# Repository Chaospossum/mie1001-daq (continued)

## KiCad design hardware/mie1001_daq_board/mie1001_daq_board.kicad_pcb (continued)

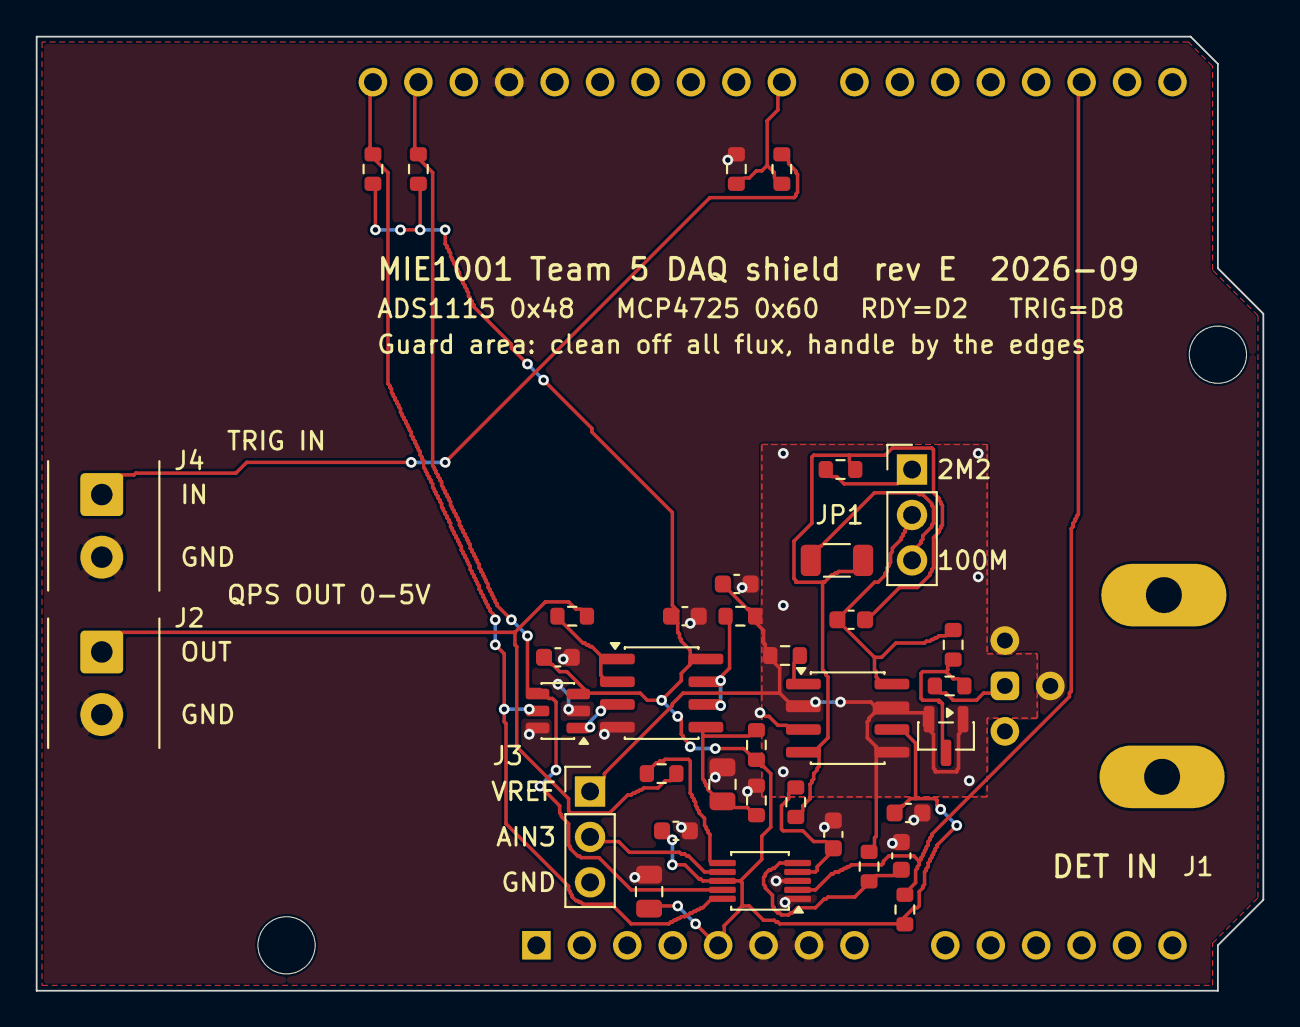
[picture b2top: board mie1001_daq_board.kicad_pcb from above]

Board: 2 copper layers, 68.6 x 53.3 mm, 40 parts (1 on the bottom side), 24 nets.

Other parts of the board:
H1, H2: MountingHole_3.2mm_M3

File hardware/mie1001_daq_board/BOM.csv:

Qty,References,Value,Footprint,Manufacturer,MPN,Digi-Key P/N,LCSC,Note
1,A1,Arduino UNO R3,Module:Arduino_UNO_R3,Arduino,A000066,1050-1024-ND,,
1,C1,10pF C0G 50V 0603,Capacitor_SMD:C_0603_1608Metric,Murata,GRM1885C1H100JA01D,490-1403-1-ND,C1634,"MUST be fitted. TIA stability needs Cf >= sqrt(Cin/(2*pi*Rf*GBW)); with ~100 pF of cable, Rf = 2M2 and the LMP7721's 17 MHz GBW that is ~0.65 pF, so 10 pF has wide margin (sets a 7.2 kHz / 159 Hz pole)."
3,"C2, C9, C10",1uF X5R 50V 0603,Capacitor_SMD:C_0603_1608Metric,Samsung,CL10A105KB8NNNC,1276-1860-1-ND,C15849,Any 1 uF >=16 V X5R/X7R 0603 works; confirm JLCPCB stock of C15849 when ordering.
2,"C3, C7",10uF X5R 25V 0805,Capacitor_SMD:C_0805_2012Metric,Samsung,CL21A106KAYNNNE,1276-2891-1-ND,C15850,
4,"C4, C5, C6, C8",100nF X7R 50V 0603,Capacitor_SMD:C_0603_1608Metric,Samsung,CL10B104KB8NNNC,1276-1000-1-ND,C14663,
1,D1,BAV199LT1G,Package_TO_SOT_SMD:SOT-23,onsemi,BAV199LT1G,BAV199LT1GOSCT-ND,C145516,"Tied to VREF, not the rails: 0 V bias means near-zero leakage into the pA node (20-50 pA per diode at 2.5 V reverse)."
1,J1,"Detector in, BNC",Connector_Coaxial:BNC_Amphenol_031-6575_Horizontal,Amphenol RF,031-6575,ARF2111-ND,,
1,J2,QPS mass cmd out,"TerminalBlock_Phoenix:TerminalBlock_Phoenix_PT-1,5-2-3.5-H_1x02_P3.50mm_Horizontal",Phoenix Contact,1984617,277-1721-ND,,
1,J3,VREF / AIN3 / GND,Connector_PinHeader_2.54mm:PinHeader_1x03_P2.54mm_Vertical,Sullins,PRPC040SAAN-RC,S1011EC-40-ND,,
1,J4,Trigger in,"TerminalBlock_Phoenix:TerminalBlock_Phoenix_PT-1,5-2-3.5-H_1x02_P3.50mm_Horizontal",Phoenix Contact,1984617,277-1721-ND,,
1,JP1,TIA range select,Connector_PinHeader_2.54mm:PinHeader_1x03_P2.54mm_Vertical,Sullins,PRPC040SAAN-RC,S1011EC-40-ND,,
1,R1,2M2 1% 0603,Resistor_SMD:R_0603_1608Metric,Yageo,RC0603FR-072M2L,YAG3329CT-ND,C22938,
1,R2,100M 1% 1206,Resistor_SMD:R_1206_3216Metric,Stackpole,HVCB1206FKC100M,HVCB1206FKC100MCT-ND,C59781,"High-value TIA feedback: guard the pads, keep them clean, no flux residue. JLC/LCSC has no HVCB stock: use Uniroyal 1206W4F1006T5E (C59781), 1% +-100 ppm/C."
6,"R3, R4, R9, R13, R16, R17",1k 1% 0603,Resistor_SMD:R_0603_1608Metric,Yageo,RC0603FR-071KL,311-1.00KHRCT-ND,C21190,Protects the LMP7721 IN+ from transients on VREF; carries only fA.
2,"R5, R6",4k7 1% 0603,Resistor_SMD:R_0603_1608Metric,Yageo,RC0603FR-074K7L,311-4.70KHRCT-ND,C23162,
4,"R7, R8, R10, R11",10k 1% 0603,Resistor_SMD:R_0603_1608Metric,Yageo,RC0603FR-0710KL,311-10.0KHRCT-ND,C25804,ALERT/RDY is open-drain - this pull-up is required
2,"R12, R15",100R 1% 0603,Resistor_SMD:R_0603_1608Metric,Yageo,RC0603FR-07100RL,311-100HRCT-ND,C22775,Isolation resistor: MCP6002 driving >100 pF of cable needs Riso (DS20001733L section 4.3). Isolation resistor so the MCP6002 VREF buffer can drive C9.
1,R14,10k 1% 0603 anti-surge,Resistor_SMD:R_0603_1608Metric,Panasonic,ERJ-PA3F1002V,P10KBYCT-ND,,"Series protection at the BNC: anti-surge (pulse-rated, AEC-Q200) 0603, limits the current into D1. 10 uV drop per nA. HAND-SOLDER from the Digi-Key order (not in the JLC assembly files)."
1,U1,MCP4725A0T-E/CH,Package_TO_SOT_SMD:SOT-23-6,Microchip,MCP4725A0T-E/CH,MCP4725A0T-E/CHCT-ND,C144198,
1,U2,ADS1115IDGSR,Package_SO:MSOP-10_3x3mm_P0.5mm,Texas Instruments,ADS1115IDGSR,296-38849-1-ND,C37593,
1,U3,MCP6002-I/SN,Package_SO:SOIC-8_3.9x4.9mm_P1.27mm,Microchip,MCP6002-I/SN,MCP6002-I/SN-ND,C116706,
1,U4,LMP7721MA/NOPB,Package_SO:SOIC-8_3.9x4.9mm_P1.27mm,Texas Instruments,LMP7721MA/NOPB,LMP7721MA/NOPB-ND,C124427,"Electrometer TIA. Guard ring (VREF) on both layers around pins 1/8 and the feedback parts, no solder mask there. Clean flux off after soldering."

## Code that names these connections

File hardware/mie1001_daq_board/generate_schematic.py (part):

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    pin("8", "VDD", -17.78, 6.35, 0, "power_in"),
    pin("9", "SDA", -17.78, 3.81, 0, "bidirectional"),
    pin("10", "SCL", -17.78, 1.27, 0, "input"),
    pin("2", "ALERT/RDY", -17.78, -1.27, 0, "open_collector"),
    pin("1", "ADDR", -17.78, -3.81, 0, "input"),
    pin("3", "GND", -17.78, -6.35, 0, "power_in"),
    pin("4", "AIN0", 17.78, 3.81, 180, "passive"),
    pin("5", "AIN1", 17.78, 1.27, 180, "passive"),
    pin("6", "AIN2", 17.78, -1.27, 180, "passive"),
    pin("7", "AIN3", 17.78, -3.81, 180, "passive"),
], {1: [rect(-12.7, 8.89, 12.7, -8.89)]},
    dict(Reference="U", Value="ADS1115IDGSR",
         Footprint="Package_SO:MSOP-10_3x3mm_P0.5mm",
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           hide_numbers=True, name_offset=0)

# ---- connectors (pins on the LEFT: signal arrives from the left, body to the right)
defsym("DAQ:BNC", [pin("1", "SIG", -11.43, 1.27, 0), pin("2", "SHIELD", -11.43, -1.27, 0),
                   # pads 3 and 4 are the other two outer-contact legs: stacked on pin 2 so all three reach GND
                   pin("3", "SHIELD", -11.43, -1.27, 0, hide=True), pin("4", "SHIELD", -11.43, -1.27, 0, hide=True)],
       {1: [rect(-6.35, 3.81, 6.35, -3.81)]},
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
R14 = place("R14", "DAQ:R", 46.99, 68.58, 90, fields=F("R14"),
            ref_at=(46.99, 64.77), val_at=(46.99, 73.66))
wire(J1.p(1), R14.p(1)); label("BNC_IN", (40.64, 68.58))   # series R before the clamp
wire(R14.p(2), (53.34, 68.58))
wire((53.34, 68.58), (53.34, 88.9))                 # down to the clamp
junction((53.34, 68.58))
label("DET_IN", (53.34, 78.74))
wire(J1.p(2), (44.45, 71.12), (44.45, 82.55)); pwr("GND", (44.45, 82.55))
# both outer ends of the BAV199 go to VREF: back-to-back clamp at 0 V bias (near-zero leakage)
wire(D1.p(1), (76.2, 90.17), (81.28, 90.17))
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text("guard = VREF", 99.06, 96.52, 1.0)
C8 = place("C8", "DAQ:C", 142.24, 93.98, fields=F("C8"), ref_at=(144.78, 92.71), val_at=(144.78, 95.25), just="left")
pwr("+5V", C8.p(1)); pwr("GND", C8.p(2))
# TIA_IN rail runs up from the inverting input and feeds JP1 pin 2 directly
wire((83.82, 68.58), (83.82, 45.72), (110.49, 45.72))
junction((83.82, 68.58))
label("TIA_IN", (83.82, 52.07))

C1 = place("C1", "DAQ:C", 93.98, 63.5, 90, fields=F("C1"),
           ref_at=(93.98, 59.69), val_at=(93.98, 67.31))
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           ref_at=(127.0, 30.48), val_at=(127.0, 35.56), just="left")
R2 = place("R2", "DAQ:R_1206", 116.84, 58.42, 90, fields=F("R2"),
           ref_at=(127.0, 55.88), val_at=(127.0, 60.96), just="left")
wire(JP1.p(1), (106.68, 43.18), (106.68, 33.02), R1.p(1)); label("RF_2M2", (106.68, 38.1))
wire(R1.p(2), (139.7, 33.02))
wire(JP1.p(3), (104.14, 48.26), (104.14, 58.42), R2.p(1)); label("RF_100M", (104.14, 53.34), justify="right bottom")
wire(R2.p(2), (139.7, 58.42))
wire((139.7, 33.02), (139.7, 71.12))                # TIA_OUT rail
junction((139.7, 58.42), (139.7, 63.5), (139.7, 71.12))
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
R3 = place("R3", "DAQ:R", 157.48, 71.12, 90, fields=F("R3"), ref_at=(157.48, 67.31), val_at=(157.48, 63.5))
C2 = place("C2", "DAQ:C", 167.64, 78.74, fields=F("C2"), ref_at=(171.45, 77.47), val_at=(171.45, 80.01), just="left")
wire(U4.p("4"), R3.p(1)); label("TIA_OUT", (146.05, 71.12))
wire(R3.p(2), (177.8, 71.12))
label("ADC_IN", (177.8, 90.17))
wire(C2.p(1), (167.64, 71.12)); junction((167.64, 71.12))
wire(C2.p(2), (167.64, 83.82)); pwr("GND", (167.64, 83.82))
text("TIA (U4 LMP7721):  Vout = VREF +/- I_det x Rf\n"
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           ref_at=(337.82, 50.8), val_at=(337.82, 59.69))
R10 = place("R10", "DAQ:R", 322.58, 62.23, fields=F("R10"), ref_at=(325.12, 60.96),
            val_at=(325.12, 63.5), just="left")
wire(J4.p(1), R9.p(2)); label("TRIG_EXT", (344.17, 54.61))
wire(R9.p(1), A1.p("23")); label("TRIG", (327.66, 54.61))
wire(J4.p(2), (349.25, 57.15), (349.25, 66.04)); pwr("GND", (349.25, 66.04))
wire(R10.p(1), (322.58, 54.61)); junction((322.58, 54.61))
wire(R10.p(2), (322.58, 72.39)); pwr("GND", (322.58, 72.39))
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wire((88.9, 132.08), (88.9, 123.19), (63.5, 123.19), U3C.p("6"))
R15 = place("R15", "DAQ:R", 96.52, 132.08, 90, fields=F("R15"),
            ref_at=(96.52, 128.27), val_at=(96.52, 136.53))
wire((88.9, 132.08), R15.p(1)); junction((88.9, 132.08)); label("VREF_BUF", (88.9, 127.0))
C9 = place("C9", "DAQ:C", 104.14, 137.16, fields=F("C9"), ref_at=(106.68, 135.89), val_at=(106.68, 138.43), just="left")
wire(C9.p(1), (104.14, 132.08)); junction((104.14, 132.08)); pwr("GND", C9.p(2))
label("VREF_DIV", (33.02, 137.16))
text("VREF = 5V x R8/(R7+R8) = 2.50 V, C3 filters USB ripple.\nU3B buffers it; R15 lets it drive C9.\nFeeds R17 -> TIA IN+, the guard, D1 and AIN1.",
     59.69, 143.51, 1.0)

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wire(U2.p("9"), (121.92, 132.08), (121.92, 101.6), (251.46, 101.6))
wire(U2.p("10"), (119.38, 134.62), (119.38, 99.06), (256.54, 99.06))
wire(U2.p("2"), (113.03, 137.16), (113.03, 110.49), (316.23, 110.49))
label("SDA", (200.66, 101.6)); label("SCL", (200.66, 99.06)); label("RDY", (200.66, 110.49))
wire(U2.p("1"), (130.81, 139.7), (130.81, 142.24), U2.p("3"))
wire((130.81, 142.24), (130.81, 149.86)); junction((130.81, 142.24))
pwr("GND", (130.81, 149.86))
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           ref_at=(207.01, 138.43), val_at=(207.01, 140.97))
R13 = place("R13", "DAQ:R", 180.34, 137.16, 90, fields=F("R13"),
            ref_at=(180.34, 140.97), val_at=(180.34, 143.51))
wire(U2.p("6"), R13.p(1)); label("AIN2", (171.45, 137.16))   # AIN2 reads back the QPS command
wire(R13.p(2), (186.69, 137.16)); label("QPS_OUT", (186.69, 137.16))
wire(U2.p("7"), (187.96, 139.7), (187.96, 148.59), J3.p(2)); label("AIN3", (187.96, 144.78), justify="right bottom")
wire(U2.p("4"), (177.8, 132.08), (177.8, 71.12))
wire(J3.p(3), (186.69, 151.13), (186.69, 158.75)); pwr("GND", (186.69, 158.75))

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R17 = place("R17", "DAQ:R", 96.52, 81.28, 0, fields=F("R17"),
            ref_at=(99.06, 80.01), val_at=(99.06, 82.55), just="left")
wire((109.22, 107.95), (96.52, 107.95), R17.p(2))    # VREF up to R17; clamp and guard tap below it
wire(R17.p(1), (96.52, 73.66), U4.p("1")); label("TIA_REF", (99.06, 73.66))
wire((109.22, 107.95), (193.04, 107.95), (193.04, 146.05), J3.p(1))
junction((109.22, 107.95))
R16 = place("R16", "DAQ:R", 187.96, 134.62, 90, fields=F("R16"),
            ref_at=(187.96, 130.81), val_at=(187.96, 138.43))
C10 = place("C10", "DAQ:C", 180.34, 130.81, 180, fields=F("C10"), ref_at=(182.88, 129.54), val_at=(182.88, 132.08), just="left")
wire(U2.p("5"), R16.p(1)); label("AIN1", (172.72, 134.62))
junction(C10.p(1)); pwr("GND", C10.p(2), 180)
junction((193.04, 134.62))
label("VREF", (140.97, 107.95))
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U3A = place("U3", "DAQ:MCP6002", 312.42, 132.08, unit=1, fields=F("U3"),
            ref_at=(311.15, 123.19), val_at=(311.15, 125.73), show_value=False)
wire(U1.p("1"), (292.1, 132.08), (292.1, 134.62), U3A.p("3"))
label("DAC_OUT", (285.75, 132.08))
wire(U3A.p("1"), (330.2, 132.08))
wire((330.2, 132.08), (330.2, 123.19), (302.26, 123.19), U3A.p("2")); label("BUF_OUT", (309.88, 123.19))
J2 = place("J2", "DAQ:Screw_Terminal_1x02", 361.95, 132.08, fields=F("J2"),
           ref_at=(361.95, 124.46), val_at=(361.95, 127.0))
R12 = place("R12", "DAQ:R", 337.82, 132.08, 90, fields=F("R12"),
            ref_at=(337.82, 128.27), val_at=(337.82, 137.16))
wire((330.2, 132.08), R12.p(1)); junction((330.2, 132.08))
wire(R12.p(2), (347.98, 132.08), (347.98, 130.81), J2.p(1))
label("QPS_OUT", (342.9, 132.08))
wire(J2.p(2), (345.44, 133.35), (345.44, 142.24)); pwr("GND", (345.44, 142.24))
text("U3A buffers the DAC (gain = 1) -> 0-5 V mass command. R12 isolates the cable.\n"
     "A 0-10 V Extrel command needs a separate >=12 V rail\n"
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 "JP1  1-2 = CEM range     Rf = R1 2M2    full scale 1.14 uA,  57 pA/LSB\n"
 "     2-3 = Faraday range Rf = R2 100M   full scale 25 nA,  1.25 pA/LSB\n"
 "I2C  ADS1115 = 0x48 (ADDR->GND)   MCP4725 = 0x60 (A0->GND)\n"
 "UNO  D2 = ALERT/RDY    D8 = trigger    SDA/SCL pins = I2C.  Every other UNO pin is free.",
 172.72, 229.87, 1.05)

# ----------------------------------------------------------------------------- emit
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
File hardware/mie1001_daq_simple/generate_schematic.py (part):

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    pin("8", "VDD", -17.78, 6.35, 0, "power_in"),
    pin("9", "SDA", -17.78, 3.81, 0, "bidirectional"),
    pin("10", "SCL", -17.78, 1.27, 0, "input"),
    pin("2", "ALERT/RDY", -17.78, -1.27, 0, "open_collector"),
    pin("1", "ADDR", -17.78, -3.81, 0, "input"),
    pin("3", "GND", -17.78, -6.35, 0, "power_in"),
    pin("4", "AIN0", 17.78, 3.81, 180, "passive"),
    pin("5", "AIN1", 17.78, 1.27, 180, "passive"),
    pin("6", "AIN2", 17.78, -1.27, 180, "passive"),
    pin("7", "AIN3", 17.78, -3.81, 180, "passive"),
], {1: [rect(-12.7, 8.89, 12.7, -8.89)]},
    dict(Reference="U", Value="ADS1115IDGSR",
         Footprint="Package_SO:MSOP-10_3x3mm_P0.5mm",
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           hide_numbers=True, name_offset=0)

# ---- connectors (pins on the LEFT: signal arrives from the left, body to the right)
defsym("DAQ:BNC", [pin("1", "SIG", -11.43, 1.27, 0), pin("2", "SHIELD", -11.43, -1.27, 0),
                   # pads 3 and 4 are the other two outer-contact legs: stacked on pin 2 so all three reach GND
                   pin("3", "SHIELD", -11.43, -1.27, 0, hide=True), pin("4", "SHIELD", -11.43, -1.27, 0, hide=True)],
       {1: [rect(-6.35, 3.81, 6.35, -3.81)]},
       dict(Reference="J", Value="BNC", Footprint="Connector_Coaxial:BNC_Amphenol_031-6575_Horizontal",
            Datasheet="", Description="BNC coaxial jack, horizontal PCB mount"))
defsym("DAQ:SMA", [pin("1", "SIG", -11.43, 1.27, 0), pin("2", "SHIELD", -11.43, -1.27, 0)],
       {1: [rect(-6.35, 3.81, 6.35, -3.81)]},
       dict(Reference="J", Value="SMA", Footprint="Connector_Coaxial:SMA_Amphenol_132134_Vertical",
            Datasheet="https://www.amphenolrf.com/132134.html",
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
# ---- ALRT/RDY: over the top of the sheet to UNO D2 on the far side
wire(U1.p(6), (XRDY, y(U1, 6)), (XRDY, 30.48), (114.3, 30.48), (A1.p("17")[0], 30.48), A1.p("17"))
label("RDY", (114.3, 30.48))

# ---- signal input: J1 -> R2 -> SIG node (D1 to +5V, D2 and C1 to GND) -> ADS1115 A0
wire(U1.p(7), (154.94, y(U1, 7)), (154.94, 60.96), (156.21, 60.96), (162.56, 60.96),
     (180.34, 60.96), (185.42, 60.96))
label("SIG", (156.21, 60.96))
D1 = place("CR1", "DAQ:D_THT", 162.56, 53.34, 90, fields=F("CR1"), ref_at=(166.37, 52.07), val_at=(166.37, 54.61), just="left")
D2 = place("CR2", "DAQ:D_THT", 162.56, 68.58, 90, fields=F("CR2"), ref_at=(166.37, 67.31), val_at=(166.37, 69.85), just="left")
C1 = place("C1", "DAQ:C_THT", 180.34, 67.31, fields=F("C1"), ref_at=(184.15, 66.04), val_at=(184.15, 68.58), just="left")
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wire(C1.p(1), (180.34, 60.96))
wire(C1.p(2), (180.34, 76.2))
wire((XGND, 76.2), (162.56, 76.2), (180.34, 76.2), (204.47, 76.2))
wire(R2.p(2), (196.85, 60.96), J1.p(1)); label("SIG_EXT", (196.85, 60.96))
wire(J1.p(2), (204.47, y(J1, 2)), (204.47, 76.2))
junction((162.56, 60.96), (180.34, 60.96), (162.56, 76.2), (180.34, 76.2))
text("INPUT PROTECTION AND FILTER", 154.94, 96.52, 1.27, bold=True)
text("R2 4.7 kΩ: limits the current into the ADC\n     if the input hits +/-12 V (2.4 mA max)\n"
     "CR1, CR2: clamp diodes, send an over-voltage to +5V or GND\n"
     "C1 100 nF: with R2 a 339 Hz low-pass filter against fast noise", 154.94, 100.33, 1.0)
text("J4 (ADS1115 inputs, not the UNO's): 1 = A1 preamp out, 2 = A2 (QPS read-back\nwhile JP1 is bridged), 3 = A3 VREF 2.5 V, 4 = GND.  Pins 1-3 are for a meter or scope only.", 184.15, 90.17, 1.0)

# ---- spare inputs A1-A3 on J4
J4 = place("J4", "DAQ:Spare_1x04", 175.26, 86.36, fields=F("J4"), ref_at=(184.15, 85.09), val_at=(184.15, 87.63), just="left")
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
# ---- QPS mass command out on J2
J2 = place("J2", "DAQ:Screw_Terminal_1x02", 175.26, 121.92, fields=F("J2"), ref_at=(175.26, 113.03), val_at=(175.26, 115.57))
wire(U2.p(1), (152.4, y(U2, 1)), J2.p(1)); label("QPS", (152.4, y(U2, 1)))
wire(J2.p(2), (XGND, y(J2, 2)))
text("QPS OUT: mass command 0-5 V\nto the Extrel controller (Team 4)\nJP1 (bridged by default) reads it back on ADS1115 A2.\nCut JP1's copper bridge to free A2 / J4-2.", 154.94, 128.27, 1.0)
JP1 = place("JP1", "DAQ:SolderJumper_2_Bridged", 157.48, 114.3,
            fields={"Value": "QPS readback", "Note": "Solder jumper, closed by a copper bridge: QPS OUT -> ADS1115 A2. Cut the bridge to use A2 (J4-2) as a free input; solder it to close again. Not a part: nothing to order."},
            ref_at=(153.67, 113.03), val_at=(153.67, 115.57), just="right")
wire(JP1.p(2), (157.48, 120.65)); junction((157.48, 120.65))
wire(JP1.p(1), (165.1, 109.22)); label("AIN2", (165.1, 109.22))

# ---- trigger in: J3 -> R1 -> UNO D8, R3 pull-down
R1 = place("R1", "DAQ:R_THT", 279.4, 142.24, 90, fields=F("R1"), ref_at=(279.4, 138.43), val_at=(279.4, 146.05))
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           ref_at=(271.78, 148.59), val_at=(271.78, 151.13), just="left")
J3 = place("J3", "DAQ:Screw_Terminal_1x02", 308.61, 143.51, fields=F("J3"), ref_at=(308.61, 134.62), val_at=(308.61, 137.16))
d8 = A1.p("23")
wire(d8, (d8[0], 142.24), (241.3, 142.24), (269.24, 142.24), R1.p(1)); label("TRIG", (241.3, 142.24))
wire(R3.p(1), (269.24, 142.24))
wire(R1.p(2), (285.75, 142.24), J3.p(1)); label("TRIG_EXT", (285.75, 142.24))
wire(J3.p(2), (292.1, y(J3, 2)), (292.1, YGB))
wire(R3.p(2), (269.24, YGB))
junction((269.24, 142.24))
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R6 = place("R6", "DAQ:R_1206", 111.76, 218.44, 90, fields=F("R6"), ref_at=(111.76, 214.63), val_at=(119.38, 214.63))
C2 = place("C2", "DAQ:C", 111.76, 223.52, 90, fields=F("C2"), ref_at=(104.14, 226.06), val_at=(119.38, 226.06))
R7 = place("R7", "DAQ:R", 91.44, 237.49, 90, fields=F("R7"), ref_at=(91.44, 241.3), val_at=(91.44, 243.84))
wire(J5.p(1), R4.p(1)); label("COAX_IN", (55.88, 232.41))
pwr("GND", J5.p(2))
wire(R4.p(2), (76.2, 232.41), R5.p(1)); junction((76.2, 232.41)); label("DET_IN", (78.74, 232.41))
wire(CR3.p(3), (76.2, 232.41))
wire(R5.p(2), (96.52, 232.41), U3.p(8)); junction((96.52, 232.41)); label("TIA_IN", (99.06, 232.41))
wire((96.52, 232.41), (96.52, 223.52), (96.52, 218.44), R6.p(1)); junction((96.52, 223.52))
wire((96.52, 223.52), C2.p(1))
wire(R6.p(2), (127.0, 218.44), (127.0, 223.52), (127.0, 234.95)); junction((127.0, 223.52), (127.0, 234.95))
wire(C2.p(2), (127.0, 223.52))
wire(R7.p(2), U3.p(1)); label("TIA_REF", (99.06, 237.49))
# output: anti-alias filter, then to ADS1115 A1 / J4-1 by the PRE_OUT label
R11 = place("R11", "DAQ:R", 137.16, 234.95, 90, fields=F("R11"), ref_at=(137.16, 231.14), val_at=(137.16, 238.76))
C6 = place("C6", "DAQ:C", 147.32, 238.76, fields=F("C6"), ref_at=(149.86, 237.49), val_at=(149.86, 240.03), just="left")
wire(U3.p(4), (127.0, 234.95), R11.p(1)); label("TIA_OUT", (129.54, 234.95))
wire(R11.p(2), (147.32, 234.95), (152.4, 234.95)); junction((147.32, 234.95)); label("PRE_OUT", (152.4, 234.95))
wire(C6.p(1), (147.32, 234.95)); pwr("GND", C6.p(2))
# LMP7721 supply, decoupling, and the N/C pins 2/5/7 on the guard (datasheet 10.1)
U3P = place("U3", "DAQ:LMP7721", 177.8, 226.06, unit=2, fields=F("U3"),
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            show_value=False)
U4P = place("U4", "DAQ:MCP6002", 281.94, 238.76, unit=3, fields=F("U4"), ref_at=(276.86, 236.22), val_at=(276.86, 241.3),
            show_value=False, just="right")
wire((213.36, 231.14), (220.98, 231.14), U4A.p(3)); junction((220.98, 231.14)); label("VREF_DIV", (215.9, 231.14))
wire(U4A.p(1), (248.92, 228.6), (248.92, 220.98), (223.52, 220.98), (223.52, 226.06), U4A.p(2))
junction((248.92, 228.6))
R10 = place("R10", "DAQ:R", 256.54, 228.6, 90, fields=F("R10"), ref_at=(256.54, 224.79), val_at=(256.54, 232.41))
wire((248.92, 228.6), R10.p(1)); label("VREF_BUF", (250.19, 228.6))
C5 = place("C5", "DAQ:C", 266.7, 232.41, fields=F("C5"), ref_at=(269.24, 233.68), val_at=(269.24, 236.22), just="left")
wire(R10.p(2), (266.7, 228.6), (271.78, 228.6), (271.78, 257.81)); junction((266.7, 228.6))
wire(C5.p(1), (266.7, 228.6)); pwr("GND", C5.p(2))
wire((220.98, 231.14), (220.98, 248.92), U4B.p(5))
wire(U4B.p(7), (248.92, 246.38), (248.92, 241.3), (223.52, 241.3), (223.52, 243.84), U4B.p(6))
label("BUF_B", (248.92, 243.84))
pwr("+5V", U4P.p(8)); pwr("GND", U4P.p(4))
C7 = place("C7", "DAQ:C", 289.56, 238.76, fields=F("C7"), ref_at=(292.1, 237.49), val_at=(292.1, 240.03), just="left")
pwr("+5V", C7.p(1)); pwr("GND", C7.p(2))
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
